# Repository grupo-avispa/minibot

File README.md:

# Minibot

An open, low-cost **differential-drive autonomous robot** built around the **ESP32** and **micro-ROS**, designed as a teaching platform for **ROS 2**. The firmware streams LiDAR scans, IMU data, and wheel odometry to a ROS 2 host over WiFi and drives the robot from `cmd_vel` commands, so students can experiment with the full SLAM → localization → navigation stack (SLAM Toolbox + Nav2) on real hardware.

Developed by the **AVISPA** research group, Department of Electronic Technology, University of Málaga.

## Features

- **micro-ROS over WiFi** — the ESP32 registers as ROS 2 nodes through a micro-ROS Agent, no USB tether required.
- **Differential drive** with two JGA25-371 DC gearmotors, Hall encoders, and a **dual PID velocity loop** for accurate odometry.
- **Sensor fusion** — wheel odometry plus a BMI160 IMU (`/imu/data_raw`) for robust pose estimation.
- **2D LiDAR** — a 3irobotix Delta-2A parsed on-device and published as `sensor_msgs/LaserScan`, with the mirror-inversion and zero-angle defects fixed in the driver.
- **Human-robot interaction** — animated OLED eyes, an RGB status LED, and DFPlayer voice feedback, driven from a `/robot_emotion` topic.
- **FreeRTOS multitasking** — separate tasks for LiDAR reading, scan publishing, and the micro-ROS executor, pinned across both ESP32 cores.
- **3D-printable chassis** — Fusion 360 source, STEP, and ready-to-print STL files, plus a custom KiCad PCB.

## Repository layout

| Path                      | Description                                                                                  |
| ------------------------- | -------------------------------------------------------------------------------------------- |
| [source/](source)         | micro-ROS firmware (single PlatformIO project): motors, encoders, IMU, LiDAR, and HRI module. |
| [designs/](designs)       | Mechanical design: Fusion 360 (`.f3z`), STEP, and printable STLs.                            |
| [schematics/](schematics) | KiCad project for the control PCB (schematic, layout, gerbers, 3D STEP).                     |
| [datasheets/](datasheets) | Component datasheets (ESP32, JGA25-371, DRV8871, BMI160, LM2596S).                           |
| [docs/](docs)             | Images and documentation assets.                                                            |

### Firmware modules — [source/](source)

| Module                                                                                | Responsibility                                                              |
| ------------------------------------------------------------------------------------- | -------------------------------------------------------------------------- |
| [jga_motors](source/src/jga_motors.cpp)         | DC motor PID control, encoder reading, odometry and `/tf`.                  |
| [bmi160_sensor](source/src/bmi160_sensor.cpp)   | BMI160 IMU acquisition and `/imu/data_raw` publishing.                      |
| [xiaomi_lidar](source/src/xiaomi_lidar.cpp)     | Delta-2A frame parsing and `/scan` publishing.                             |
| [emotions](source/src/emotions.cpp)             | OLED eyes, RGB LED, and voice feedback driven from `/robot_emotion`.        |
| [main.cpp](source/src/main.cpp)                 | micro-ROS entities, time sync, FreeRTOS tasks, and reconnection handling.  |

## Hardware

- **MCU board:** ESP32-WROOM-32 — ESP32 DevKit C V4 (USB-C), PlatformIO board `az-delivery-devkit-v4`
- **Motors:** 2× JGA25-371 DC gearmotors with Hall quadrature encoders
- **Motor driver:** DRV8871 H-bridge (per motor), 2-pin PWM control
- **LiDAR:** 3irobotix Delta-2A 2D scanner (≈0.13–8 m), UART TTL 3.3 V
- **IMU:** Bosch BMI160 6-axis (I²C, address `0x69`)
- **Power:** 3S Li-Ion 18650 pack with BMS (≈11.1 V) → 12 V to motors; LM2596S buck converter → 5 V rail for ESP32 and LiDAR
- **HRI:** 2× SSD1306 OLED displays, RGB LED, DFPlayer Mini audio
- **Chassis & PCB:** 3D-printed body (PLA + TPU, see [designs/](designs)) on a custom KiCad PCB (see [schematics/](schematics))

Datasheets for the main components are in [datasheets/](datasheets).

### Pinout (ESP32 GPIO)

| Subsystem        | Signal                        | GPIO                    |
| ---------------- | ----------------------------- | ----------------------- |
| Left motor       | IN1 / IN2 (PWM)               | 21 / 19                 |
| Left encoder     | A / B                         | 32 / 33                 |
| Right motor      | IN1 / IN2 (PWM)               | 4 / 27                  |
| Right encoder    | A / B                         | 34 / 35                 |
| Encoder LEDs     | Red / Blue                    | 16 / 17                 |
| LiDAR            | UART RX (Serial2) / motor enable | 26 / 25              |
| IMU + OLED (I²C) | SDA / SCL                     | 13 / 14                 |
| RGB LED          | R / G / B                     | 15 / 12 / 22            |
| DFPlayer (audio) | RX / TX                       | 18 / 5                  |

Pin assignments are defined at the top of each module ([jga_motors.hpp](source/include/jga_motors.hpp), [emotions.hpp](source/include/emotions.hpp)) and in the corresponding `.cpp` files.

### Robot constants

- Wheel radius: `0.0427 m`
- Wheel base (track width): `0.2195 m`
- Encoder ticks per wheel revolution: `1980`
- Speed range: `0.08 – 0.3 m/s`
- PID gains (per wheel): `kp = 0.8`, `ki = 0.4`, `kd = 0.1`

## Requirements

- [PlatformIO](https://platformio.org/) (CLI or the VS Code extension)
- A ROS 2 installation on the host (firmware targets **Jazzy**)
- A running **micro-ROS Agent** on the host

## Configuration

Edit the WiFi credentials and the micro-ROS Agent endpoint in [source/config/uros_wifi_config.h](source/config/uros_wifi_config.h):

```cpp
char ssid[] = "your-wifi-ssid";
char psk[]  = "your-wifi-password";

IPAddress agent_ip(192, 168, 0, 100);   // host running the micro-ROS Agent
size_t    agent_port = 8888;
```

Review the hardware pins (see [pinout](#pinout-esp32-gpio) above) and, if needed, the robot dimensions and PID gains in [jga_motors.hpp](source/include/jga_motors.hpp).

The firmware ships a [custom.meta](source/custom.meta) that raises the micro-XRCE-DDS transport MTU and entity limits — keep it in sync if you add publishers/subscriptions.

## Build, flash and monitor

[source/](source) is a PlatformIO project. From that directory:

```bash
cd source

pio run                        # compile
pio run -t upload              # flash over USB
pio device monitor -b 115200   # open the serial monitor
```

## Running with ROS 2

1. Start the micro-ROS Agent on your ROS 2 host (matching the IP/port configured in firmware):

   ```bash
   ros2 run micro_ros_agent micro_ros_agent udp4 --port 8888
   ```

2. Power on the ESP32. It connects to WiFi, registers its nodes with the Agent, and synchronizes its clock with the host. If the Agent becomes unreachable it stops the motors and recreates its ROS entities automatically.
3. Inspect the graph:

   ```bash
   ros2 topic list
   ros2 topic echo /scan
   ```

### Topics and frames

Nodes: `minibot_lidar` and `minibot_jga`.

| Direction | Topic            | Type                    |
| --------- | ---------------- | ----------------------- |
| Publish   | `/scan`          | `sensor_msgs/LaserScan` |
| Publish   | `/odom`          | `nav_msgs/Odometry`     |
| Publish   | `/imu/data_raw`  | `sensor_msgs/Imu`       |
| Publish   | `/tf`            | `tf2_msgs/TFMessage`    |
| Subscribe | `/cmd_vel`       | `geometry_msgs/Twist`   |
| Subscribe | `/robot_emotion` | `std_msgs/Int32`        |

Frames: `odom` → `base_link`, plus `base_laser_link` for the scan.

Drive the robot with, for example:

```bash
ros2 run teleop_twist_keyboard teleop_twist_keyboard
```

## Mechanical design

3D models live in [designs/](designs):

- `Fusion/Robotito v3.f3z` — editable Fusion 360 source
- `STEP/Robotito v3.step` — neutral CAD exchange format
- `STLs/` — printable parts (main body, wheels and tires, caster wheel + support, motor clamps, LiDAR support, PCB support and spacers, front face)

The control PCB (KiCad project, gerbers, and a 3D STEP export) is in [schematics/](schematics).

## Implementation notes

- The firmware runs dedicated FreeRTOS tasks for LiDAR serial parsing, `LaserScan` assembly/publishing, and the micro-ROS executor, pinned across both cores.
- Motor speed is closed-loop: encoder ticks feed a per-wheel PID with a state machine for smooth start/stop and braking.
- Odometry is integrated from encoder counts and published with the `odom` → `base_link` TF; the BMI160 adds orientation data on `/imu/data_raw`.
- The Delta-2A driver corrects the original mirror inversion and uses a start-angle zero-crossing detector for consistent scan framing.
- A periodic sync timer aligns the ESP32 clock with the micro-ROS Agent so message timestamps are valid on the host.

## License

This project — firmware, mechanical designs, schematics, and documentation — is licensed under the **Creative Commons Attribution-NonCommercial-ShareAlike 4.0 International License (CC BY-NC-SA 4.0)**.

You are free to **share** and **adapt** the material for **non-commercial** purposes, provided you give appropriate **credit** and license your derivatives under the **same** terms. Commercial use requires prior written permission from the author.

See [LICENSE](LICENSE) for the full text · [License summary](https://creativecommons.org/licenses/by-nc-sa/4.0/)

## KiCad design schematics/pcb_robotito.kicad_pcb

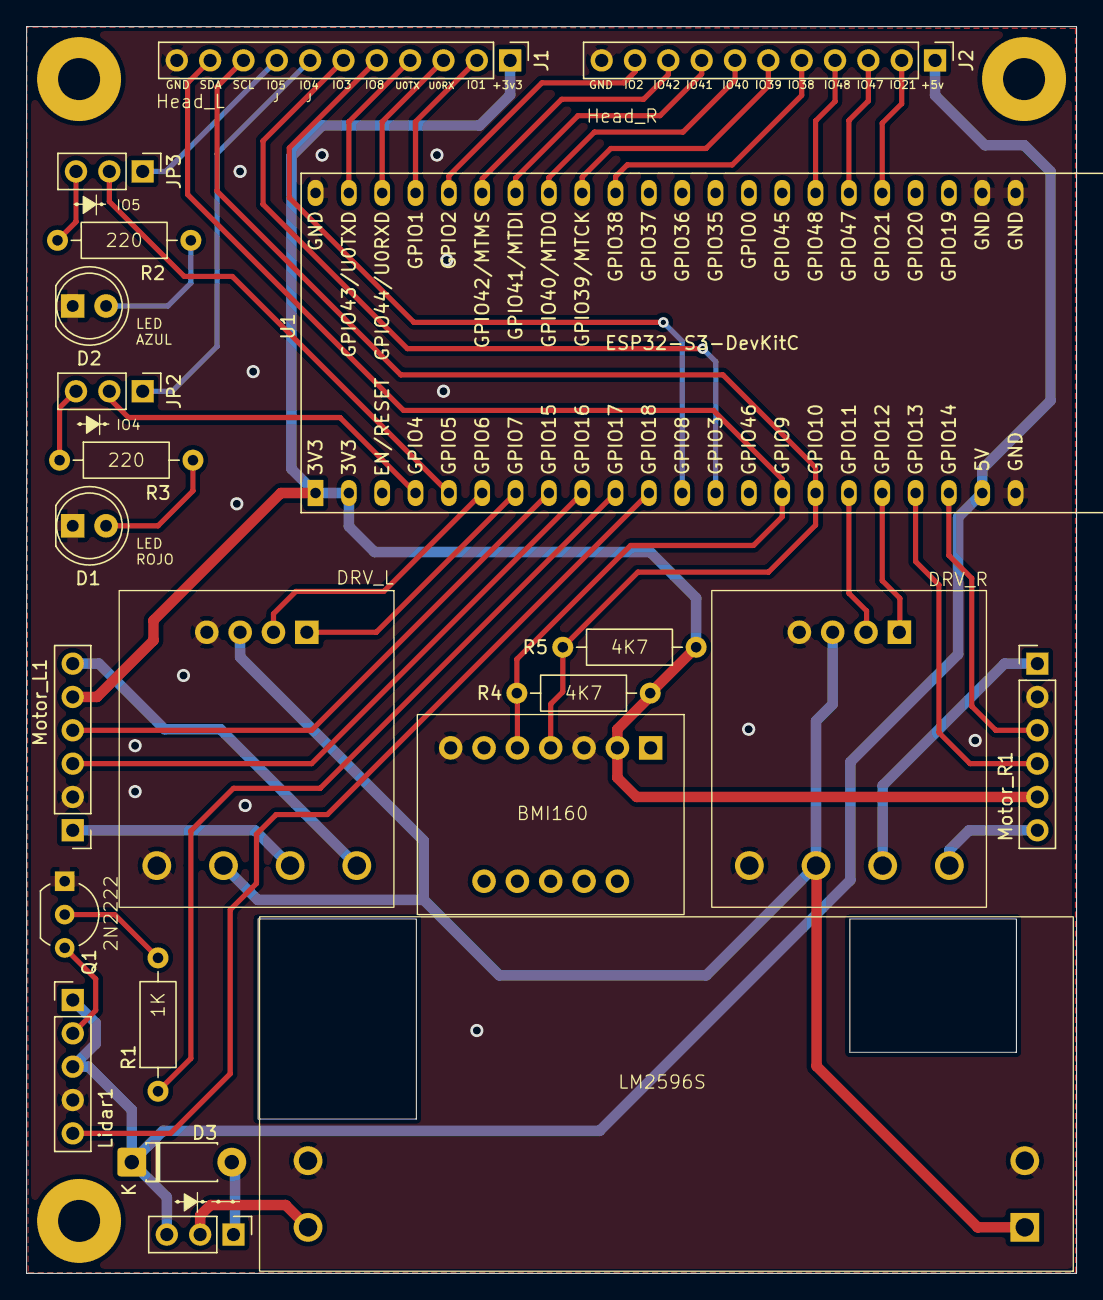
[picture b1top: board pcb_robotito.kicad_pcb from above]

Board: 2 copper layers, 80.0 x 95.0 mm, 25 parts (0 on the bottom side), 46 nets.

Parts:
BMI1: BMI160
D1: LED_rojo; LED_D5.0mm
D2: LED_azul; LED_D5.0mm
D3: Diodo; D_DO-41_SOD81_P7.62mm_Horizontal
DRV_L1: DRV8871
DRV_R1: DRV8871
J1: Head_L; PinHeader_1x11_P2.54mm_Vertical
J2: Head_R; PinHeader_1x11_P2.54mm_Vertical
JP1, JP2, JP3: Jumper_3_Open; PinHeader_1x03_P2.54mm_Vertical
LM2596S1: LM2596S
Lidar1: PinHeader_1x05_P2.54mm_Vertical
Motor_L1: PinHeader_1x06_P2.54mm_Vertical
Motor_R1: PinHeader_1x06_P2.54mm_Vertical
Q1: PN2222A; TO-92_Inline_Wide
R1: R_1k; R_Axial_DIN0207_L6.3mm_D2.5mm_P10.16mm_Horizontal
R2, R3: R_220; R_Axial_DIN0207_L6.3mm_D2.5mm_P10.16mm_Horizontal
R4, R5: R_4K7; R_Axial_DIN0207_L6.3mm_D2.5mm_P10.16mm_Horizontal
U1: ESP32-S3-DevKitC
tornillo1, tornillo3, tornillo4: MountingHole_3.2mm_M3_Pad

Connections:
+3V3: BMI1.2 (3V3), J1.1, Motor_L1.5 (AZUL), Motor_R1.5 (AZUL), R4.1, R5.1, U1.1 (3V3), U1.2 (3V3)
+5V: D3.1 (K), J2.1, JP1.3 (B), Lidar1.1 (+), Lidar1.3 (V), U1.21 (5V)
+12V: DRV_L1.3 (VM), DRV_L1.6 (VM), DRV_R1.3 (VM), DRV_R1.6 (VM), LM2596S1.1 (12V)
/ENC_A_L: Motor_L1.3 (YELLOW), U1.9 (GPIO16/ADC2_CH5/32K_N)
/ENC_A_R: Motor_R1.3 (YELLOW), U1.20 (GPIO14/ADC2_CH3)
/ENC_B_L: Motor_L1.4 (GREEN), U1.8 (GPIO15/ADC2_CH4/32K_P)
/ENC_B_R: Motor_R1.4 (GREEN), U1.19 (GPIO13/ADC2_CH2)
/GPIO1: J1.2, U1.41 (GPIO1/ADC1_CH0)
/GPIO2: J2.10, U1.40 (GPIO2/ADC1_CH1)
/GPIO3: J1.6, U1.13 (GPIO3/ADC1_CH2)
/GPIO4: JP2.2 (C), U1.4 (GPIO4/ADC1_CH3)
/GPIO5: JP3.2 (C), U1.5 (GPIO5/ADC1_CH4)
/GPIO8: J1.5, U1.12 (GPIO8/ADC1_CH7)
/GPIO21: J2.2, U1.27 (GPIO21)
/GPIO38: J2.5, U1.35 (GPIO38)
/GPIO39: J2.6, U1.36 (GPIO39/MTCK)
/GPIO40: J2.7, U1.37 (GPIO40/MTDO)
/GPIO41: J2.8, U1.38 (GPIO41/MTDI)
/GPIO42: J2.9, U1.39 (GPIO42/MTMS)
/GPIO47: J2.3, U1.28 (GPIO47)
/GPIO48: J2.4, U1.29 (GPIO48)
/IN1_L: DRV_L1.2 (IN1), U1.6 (GPIO6/ADC1_CH5)
/IN1_R: DRV_R1.2 (IN1), U1.17 (GPIO11/ADC2_CH0)
/IN2_L: DRV_L1.1 (IN2), U1.7 (GPIO7/ADC1_CH6)
/IN2_R: DRV_R1.1 (IN2), U1.18 (GPIO12/ADC2_CH1)
/J_GPIO4: J1.7, JP2.1 (A)
/J_GPIO5: J1.8, JP3.1 (A)
/LIDAR_EN: R1.1, U1.10 (GPIO17/ADC2_CH6)
/M1L: DRV_L1.7 (M1), Motor_L1.1 (RED)
/M1R: DRV_R1.7 (M1), Motor_R1.1 (RED)
/M2L: DRV_L1.8 (M2), Motor_L1.6 (WHITE)
/M2R: DRV_R1.8 (M2), Motor_R1.6 (WHITE)
/SCL: BMI1.4 (SCL), J1.9, R5.2, U1.16 (GPIO10/ADC1_CH9)
/SDA: BMI1.5 (SDA), J1.10, R4.2, U1.15 (GPIO9/ADC1_CH8)
/U0RXD: J1.3, U1.42 (GPIO44/U0RXD)
/U0TXD: J1.4, U1.43 (GPIO43/U0TXD)
/U2RXD: Lidar1.5 (T), U1.11 (GPIO18/ADC2_CH7)
GND: BMI1.3 (GND), BMI1.7 (SAO), D1.1 (K), D2.1 (K), DRV_L1.4 (GND), DRV_L1.5 (GND), DRV_R1.4 (GND), DRV_R1.5 (GND), J1.11, J2.11, LM2596S1.2 (GND), LM2596S1.3 (GND), Lidar1.4 (G), Motor_L1.2 (BLACK), Motor_R1.2 (BLACK), Q1.1 (E), U1.22 (GND), U1.23 (GND), U1.24 (GND), U1.44 (GND)
unnamed: D1.2 (A), R3.2
unnamed: D2.2 (A), R2.1
unnamed: D3.2 (A), JP1.1 (A)
unnamed: JP1.2 (C), LM2596S1.4 (5V)
unnamed: JP2.3 (B), R3.1
unnamed: JP3.3 (B), R2.2
unnamed: Lidar1.2 (-), Q1.3 (C)
unnamed: Q1.2 (B), R1.2

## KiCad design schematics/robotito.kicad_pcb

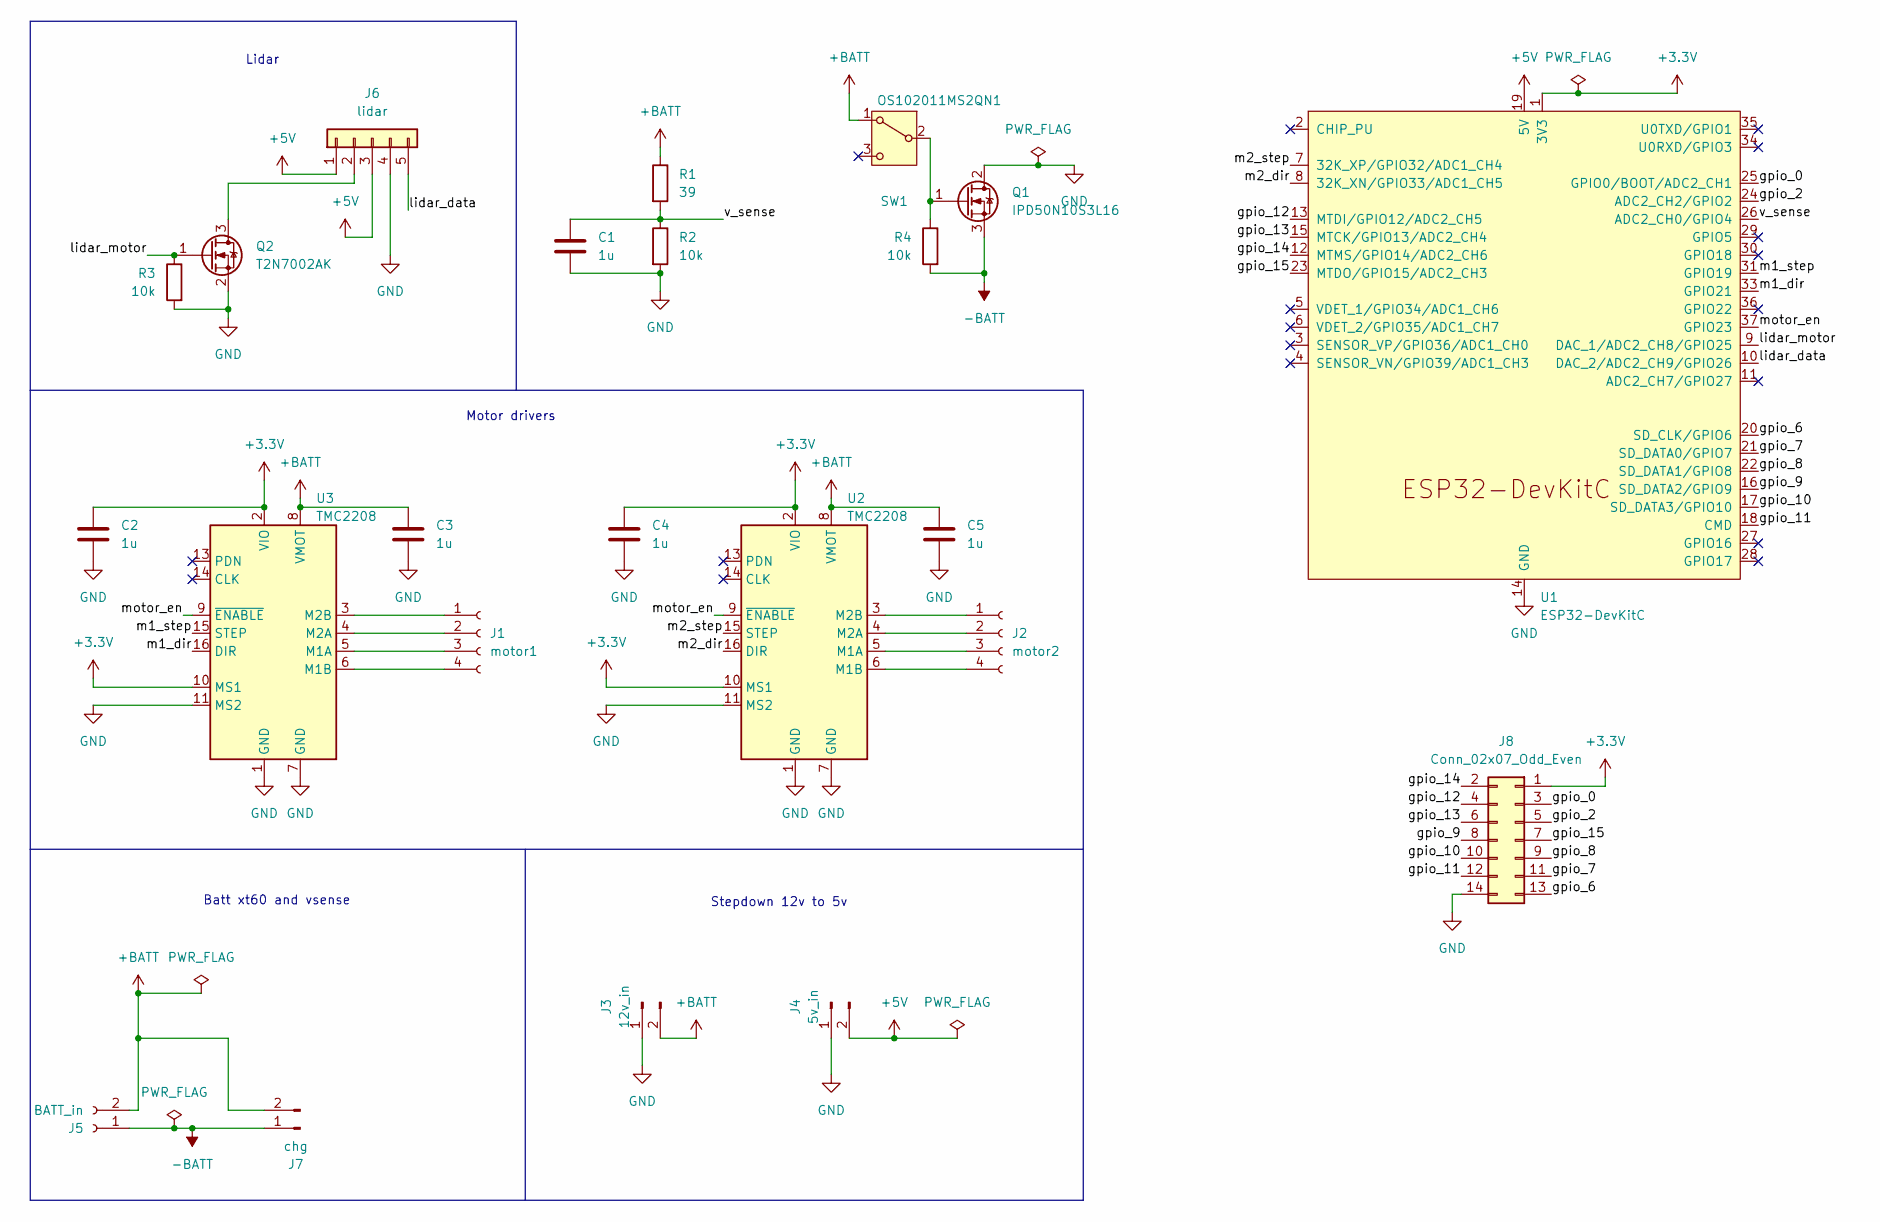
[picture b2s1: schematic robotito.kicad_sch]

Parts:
C1, C2, C3, C4, C5: 1u; C_0805_2012Metric_Pad1.18x1.45mm_HandSolder
J1: motor1; PinHeader_1x04_P2.54mm_Vertical
J2: motor2; PinHeader_1x04_P2.54mm_Vertical
J3: 12v_in; PinSocket_1x02_P2.54mm_Vertical
J4: 5v_in; PinSocket_1x02_P2.54mm_Vertical
J5: BATT_in; AMASS_XT60-F_1x02_P7.20mm_Vertical
J6: lidar; PinHeader_1x05_P2.54mm_Vertical
J7: chg; PinSocket_1x02_P2.54mm_Vertical
J8: Conn_02x07_Odd_Even; PinSocket_2x07_P2.54mm_Vertical
Q1: IPD50N10S3L16; TO-252-2
Q2: T2N7002AK; SOT-23
R1: 39; R_0805_2012Metric_Pad1.20x1.40mm_HandSolder
R2, R3, R4: 10k; R_0805_2012Metric_Pad1.20x1.40mm_HandSolder
SW1: OS102011MS2QN1
U1: ESP32-DevKitC
U2, U3: TMC2208; Pololu_Breakout-16_15.2x20.3mm

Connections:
+3.3V: C2.1, C4.1, J8.1, U1.1 (3V3), U2.2 (VIO), U2.10 (MS1), U3.2 (VIO), U3.10 (MS1)
+5V: J4.2, J6.1, J6.3, U1.19 (5V)
+BATT: C3.1, C5.1, J3.2, J5.2, J7.2, R1.1, SW1.1 (A), U2.8 (VMOT), U3.8 (VMOT)
-BATT: J5.1, J7.1, Q1.3 (S), R4.2
/gpio_0: J8.3, U1.25 (GPIO0/BOOT/ADC2_CH1)
/gpio_2: J8.5, U1.24 (ADC2_CH2/GPIO2)
/gpio_6: J8.13, U1.20 (SD_CLK/GPIO6)
/gpio_7: J8.11, U1.21 (SD_DATA0/GPIO7)
/gpio_8: J8.9, U1.22 (SD_DATA1/GPIO8)
/gpio_9: J8.8, U1.16 (SD_DATA2/GPIO9)
/gpio_10: J8.10, U1.17 (SD_DATA3/GPIO10)
/gpio_11: J8.12, U1.18 (CMD)
/gpio_12: J8.4, U1.13 (MTDI/GPIO12/ADC2_CH5)
/gpio_13: J8.6, U1.15 (MTCK/GPIO13/ADC2_CH4)
/gpio_14: J8.2, U1.12 (MTMS/GPIO14/ADC2_CH6)
/gpio_15: J8.7, U1.23 (MTDO/GPIO15/ADC2_CH3)
/lidar_data: J6.5, U1.10 (DAC_2/ADC2_CH9/GPIO26)
/lidar_motor: Q2.1 (G), R3.1, U1.9 (DAC_1/ADC2_CH8/GPIO25)
/m1_dir: U1.33 (GPIO21), U3.16 (DIR)
/m1_step: U1.31 (GPIO19), U3.15 (STEP)
/m2_dir: U1.8 (32K_XN/GPIO33/ADC1_CH5), U2.16 (DIR)
/m2_step: U1.7 (32K_XP/GPIO32/ADC1_CH4), U2.15 (STEP)
/motor_en: U1.37 (GPIO23), U2.9 (~ENABLE), U3.9 (~ENABLE)
/v_sense: C1.1, R1.2, R2.1, U1.26 (ADC2_CH0/GPIO4)
GND: C1.2, C2.2, C3.2, C4.2, C5.2, J3.1, J4.1, J6.4, J8.14, Q1.2 (D), Q2.2 (S), R2.2, R3.2, U1.14 (GND), U1.32 (GND), U1.38 (GND), U2.1 (GND), U2.7 (GND), U2.11 (MS2), U3.1 (GND), U3.7 (GND), U3.11 (MS2)
unnamed: J1.1, U3.3 (M2B)
unnamed: J1.2, U3.4 (M2A)
unnamed: J1.3, U3.5 (M1A)
unnamed: J1.4, U3.6 (M1B)
unnamed: J2.1, U2.3 (M2B)
unnamed: J2.2, U2.4 (M2A)
unnamed: J2.3, U2.5 (M1A)
unnamed: J2.4, U2.6 (M1B)
unnamed: J6.2, Q2.3 (D)
unnamed: Q1.1 (G), R4.1, SW1.2 (B)

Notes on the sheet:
Batt xt60 and vsense
Lidar
Motor drivers
Stepdown 12v to 5v

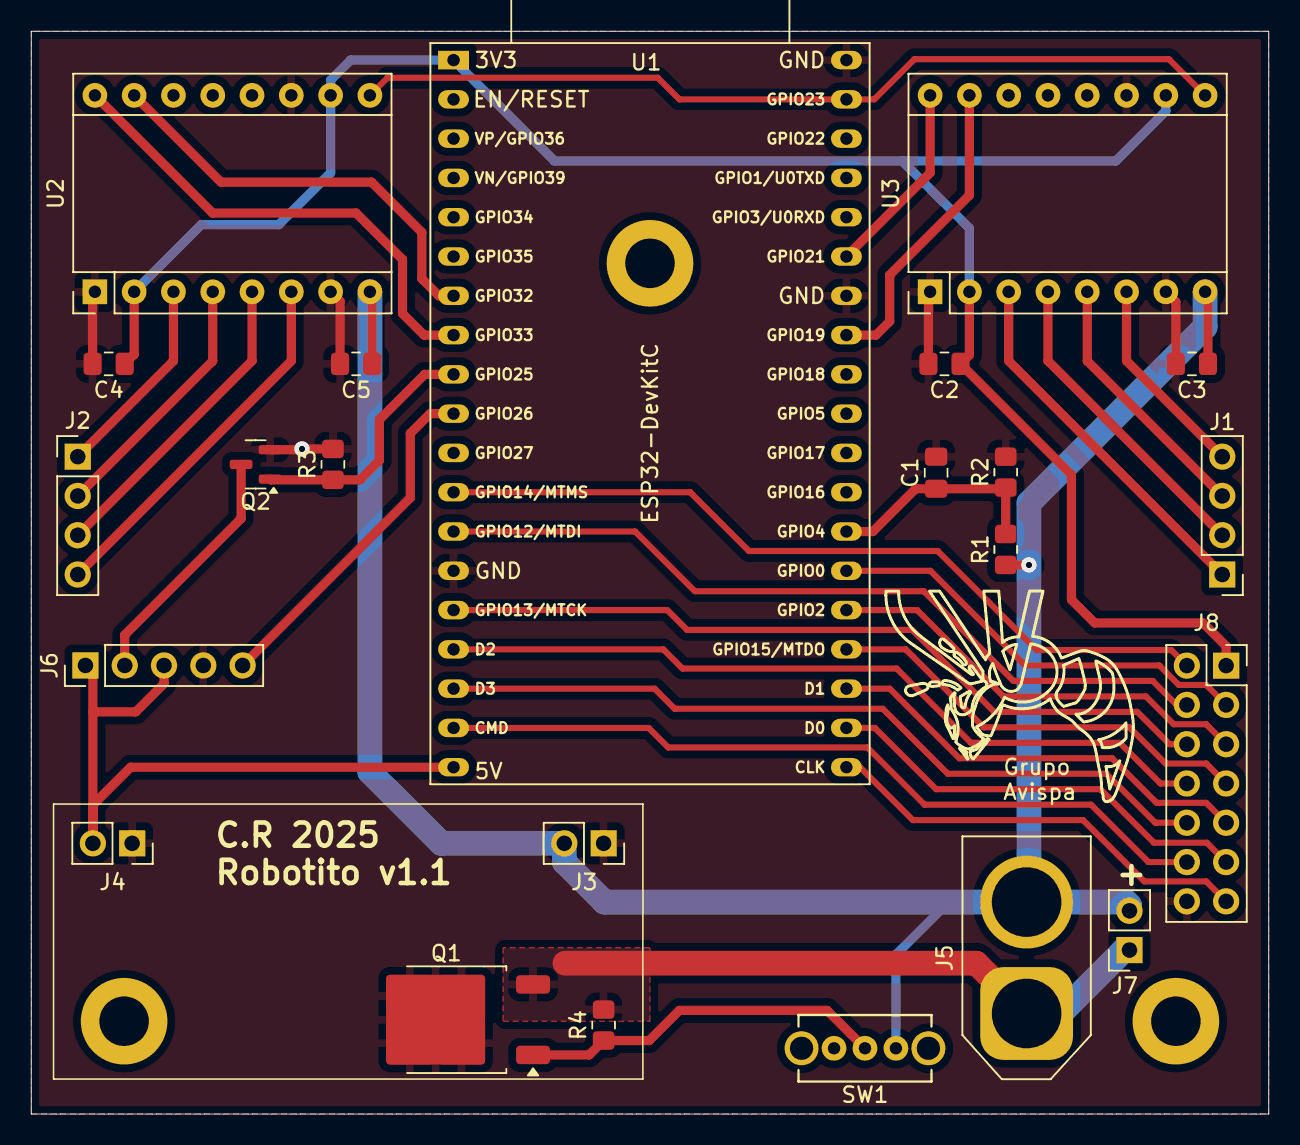
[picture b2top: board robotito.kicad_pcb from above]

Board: 2 copper layers, 80.0 x 70.0 mm, 23 parts (0 on the bottom side), 35 nets.

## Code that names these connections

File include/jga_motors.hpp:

#ifndef JGAMOTORS_HPP
#define JGAMOTORS_HPP

#include <Arduino.h>
#include <FS_MX1508.h>
#include <ESP32Encoder.h>

#include <rcl/rcl.h>
#include <rclc/rclc.h>
#include <nav_msgs/msg/odometry.h>
#include <geometry_msgs/msg/twist.h>
#include <tf2_msgs/msg/tf_message.h>

// --- MÁQUINA DE ESTADOS ---
enum EstadoSistema {
    ESTADO_NORMAL,   // PID trabajando con normalidad
    ESTADO_PARANDO,  // Bajando velocidad hasta VEL_MIN_MS antes de frenar
    ESTADO_FRENO,    // Poniendo PWM a 0 y reseteando PID
    ESTADO_STOPPED   // Parado en seco, esperando comando
};

// --- IMPLEMENTACIÓN DEL PID (.ino) ---
struct CustomPID {
    float kp, ki, kd;
    float e_n1, e_n2, r_n1;
    float outMin, outMax;

    CustomPID(float p, float i, float d) {
        kp = p; ki = i; kd = d;
        e_n1 = 0.0f; e_n2 = 0.0f; r_n1 = 0.0f;
        outMin = -255.0f; outMax = 255.0f;
    }

    void setTunings(float p, float i, float d) {
        kp = p; ki = i; kd = d;
    }

    void reset() {
        e_n1 = 0.0f; e_n2 = 0.0f; r_n1 = 0.0f;
    }

    float compute(float setpoint, float input) {
        float e_n = setpoint - input;
        float r_n = r_n1 + kp * (e_n - e_n1) + ki * (e_n + e_n1) / 2.0f + kd * (e_n - 2.0f * e_n1 + e_n2);
        
        if (r_n > outMax) r_n = outMax;
        if (r_n < outMin) r_n = outMin;

        e_n2 = e_n1;
        e_n1 = e_n;
        r_n1 = r_n;

        return r_n;
    }
};

// =============================================================================
//  JgaMotors
// =============================================================================
class JgaMotors {
public:
    JgaMotors();
    ~JgaMotors();

    void init();
    void emergency_stop();
    void cmd_vel_sub_callback(const void *msgin);
    void timer_odometry_callback(rcl_timer_t *timer, int64_t last_call_time);
    void update_pose(long deltaTicks_l, long deltaTicks_r);

    // ── ROS ──────────────────────────────────────────────────────────────────
    rcl_publisher_t    odom_pub;
    rcl_publisher_t    tf_pub;
    rcl_subscription_t cmd_vel_sub;
    rcl_timer_t        timer_odom;

    nav_msgs__msg__Odometry    odom_msg;
    tf2_msgs__msg__TFMessage   tf_msg;
    geometry_msgs__msg__Twist  cmd_vel_msg;

    // ── Sincronización de tiempo micro-ROS ────────────────────────────────────
    int64_t ros_synced_time_ms = 0;
    int64_t ros_synced_time_ns = 0;
    long    ms_before_sync     = 0;

private:
    float msToRPM(float m_s);
    int aplicarZonaMuerta(int pwm);
    void resetPID();
    void arrancarMotor(float sp_l, float sp_r);

    // ─────────────────────────────────────────────────────────────────────────
    //  PINES
    // ─────────────────────────────────────────────────────────────────────────
    static const int IN1_L   = 21;
    static const int IN2_L   = 19;
    static const int ENC_A_L = 32;
    static const int ENC_B_L = 33;

    static const int IN1_R   = 4;
    static const int IN2_R   = 27;
    static const int ENC_A_R = 34;   
    static const int ENC_B_R = 35;   

    static const int LED_RED  = 16;
    static const int LED_BLUE = 17;

    // ─────────────────────────────────────────────────────────────────────────
    //  CONFIGURACIÓN FÍSICA Y LÍMITES
    // ─────────────────────────────────────────────────────────────────────────
    static const int MIN_PWM_REAL = 40;
    static constexpr float TICKS_POR_VUELTA = 1980.0f;  
    static constexpr float RADIO_RUEDA_M = 0.0425f;  
    static constexpr float PERIMETRO_RUEDA_M = 2.0f * PI * RADIO_RUEDA_M;
    static constexpr float WHEEL_BASE = 0.225f;

    float VEL_MIN_MS = 0.08f;
    float VEL_MAX_MS = 0.3f;

    static const int PERIODO_MS = 40;
    static constexpr float ALPHA = 0.4f;
    static constexpr float RAMPA_CAMBIO_RPM = 10.0f;
    static constexpr float BANDA_MUERTA_RPM = 2.0f;
    static const int CICLOS_ARRANQUE = 3;

    // ─────────────────────────────────────────────────────────────────────────
    //  HARDWARE & PID
    // ─────────────────────────────────────────────────────────────────────────
    MX1508      *motor_l = nullptr;
    MX1508      *motor_r = nullptr;
    ESP32Encoder encoder_l;
    ESP32Encoder encoder_r;

    float global_kp = 0.8f;
    float global_ki = 0.4f;
    float global_kd = 0.1f;

    CustomPID pid_l{global_kp, global_ki, global_kd};
    CustomPID pid_r{global_kp, global_ki, global_kd};

    // ─────────────────────────────────────────────────────────────────────────
    //  ESTADO DEL SISTEMA (VARIABLES DEL .ino)
    // ─────────────────────────────────────────────────────────────────────────
    EstadoSistema estadoActual = ESTADO_STOPPED;

    float rpmFiltrado_l = 0.0f;
    float rpmFiltrado_r = 0.0f;

    long posAnterior_l = 0;
    long posAnterior_r = 0;

    float setpointRampaRPM_l    = 0.0f;
    float setpointRampaRPM_r    = 0.0f;
    float setpointObjetivoRPM_l = 0.0f;
    float setpointObjetivoRPM_r = 0.0f;
    
    unsigned long tAnterior = 0;

    int signoAnterior_l = 0;
    int signoAnterior_r = 0;
    int ciclosArranque_l = 0;
    int ciclosArranque_r = 0;

    // ─────────────────────────────────────────────────────────────────────────
    //  POSE ODOMÉTRICA
    // ─────────────────────────────────────────────────────────────────────────
    float x     = 0.0f;
    float y     = 0.0f;
    float theta = 0.0f;
};

#endif // JGAMOTORS_HPP

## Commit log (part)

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2026-02-23 Update with full code
2026-02-25 Remove folders
2026-03-04 update gitignore
2026-03-05 Fixed jazzy distro platformio.ini
2026-03-05 Added uros_wifi_config.h
2026-03-10 IMU implementation (WIP)
2026-03-20 JGA motors in uros implemented (WIP)
2026-03-23 JGA Motors PID implemented (WIP)
2026-04-08 Improvement FIX for motor PID
2026-04-08 fixed imu name for Nav2
2026-04-08 updated main for Nav2
2026-04-15 Robotito + Nav2
2026-04-21 uros_config UPDATED
2026-05-18 Emotion module implementation
2026-06-11 Move code to source
2026-06-11 Added datasheets, designs, etc
2026-06-11 Update datasheets and designs for v3
2026-06-11 Move to source
2026-06-11 Fix merge
2026-06-11 Update copyright
2026-06-11 Added license to source files
